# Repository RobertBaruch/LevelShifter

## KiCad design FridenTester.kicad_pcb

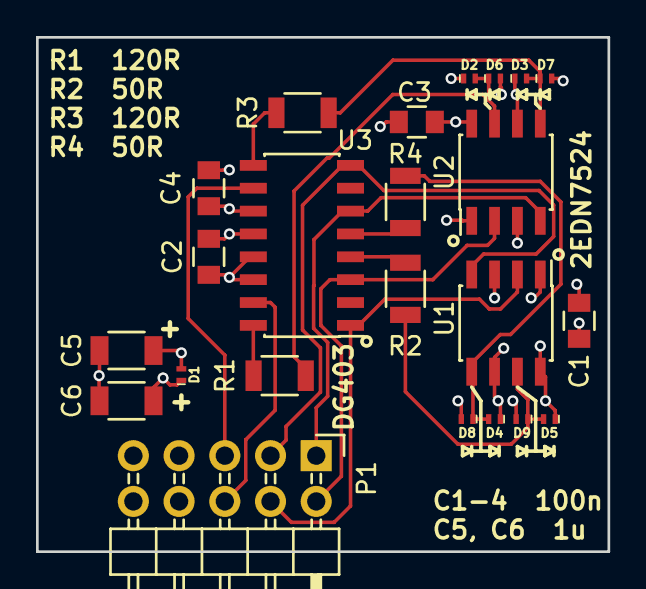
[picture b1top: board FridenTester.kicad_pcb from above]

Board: 4 copper layers, 31.7 x 28.6 mm, 23 parts (0 on the bottom side), 17 nets.

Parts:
C1, C2, C3, C4: 100n; C_0805
C5, C6: 1u; C_1206
D1, D2, D3, D4, D5, D6, D7, D8, D9: CFSH05; SOD-882L
P1: CONN_02X05; Pin_Header_Angled_2x05
R1, R3: 120; R_1206
R2, R4: 50; R_1206
U1, U2: 2EDN752; SOIC-8_3.9x4.9mm_Pitch1.27mm
U3: DG403; SOIC-16_3.9x9.9mm_Pitch1.27mm

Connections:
+12V: C3.1, C4.1, C6.1, D1.1, D2.1, D3.1, P1.8, U2.1, U2.6, U2.8, U3.11
/IO5A: P1.2, U2.2, U3.3
/IO5B: P1.1, U2.4, U3.6
/IO12A: P1.4, U1.2, U3.1
/IO12B: P1.3, U1.4, U3.8
/OUT5A: D5.2, D9.1, R2.1, U1.7
/OUT5B: D4.2, D8.1, R4.2, U1.5
/OUT12A: D2.2, D6.1, R1.1, U2.7
/OUT12B: D3.2, D7.1, R3.2, U2.5
/SW_A: P1.6, U3.15
/SW_B: P1.5, U3.10
GNDREF: C1.2, C2.2, C3.2, C4.2, C5.2, C6.2, D6.2, D7.2, D8.2, D9.2, P1.9, P1.10, U1.3, U2.3, U3.13, U3.14
unnamed: R1.2, U3.16
unnamed: R2.2, U3.4
unnamed: R3.1, U3.9
unnamed: R4.1, U3.5
VDD: C1.1, C2.1, C5.1, D1.2, D4.1, D5.1, P1.7, U1.1, U1.6, U1.8, U3.12

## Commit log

2016-10-13 :circus_tent: Added .gitattributes & .gitignore files
2016-10-29 Version B (version A had bad pinouts for NMOS)
2016-11-01 Adds solder paste stencil for version B
2016-11-01 Added text, images
2016-11-03 Revision C, with gate drivers instead of mosfets
2016-11-04 Adds rev C schematic PDF
2016-11-04 Change rev on schematic
2016-11-18 Start on rev D, with protection Schottkys
2016-11-19 Revision D board layout
2016-11-19 Corrects NO/NC switch settings on DG403 chip
2016-12-03 Adds some data sheets
